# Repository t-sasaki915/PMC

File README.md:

# PrimitiveMemoryComputer
An AVR-based 8-bit single-board computer for direct memory programming.

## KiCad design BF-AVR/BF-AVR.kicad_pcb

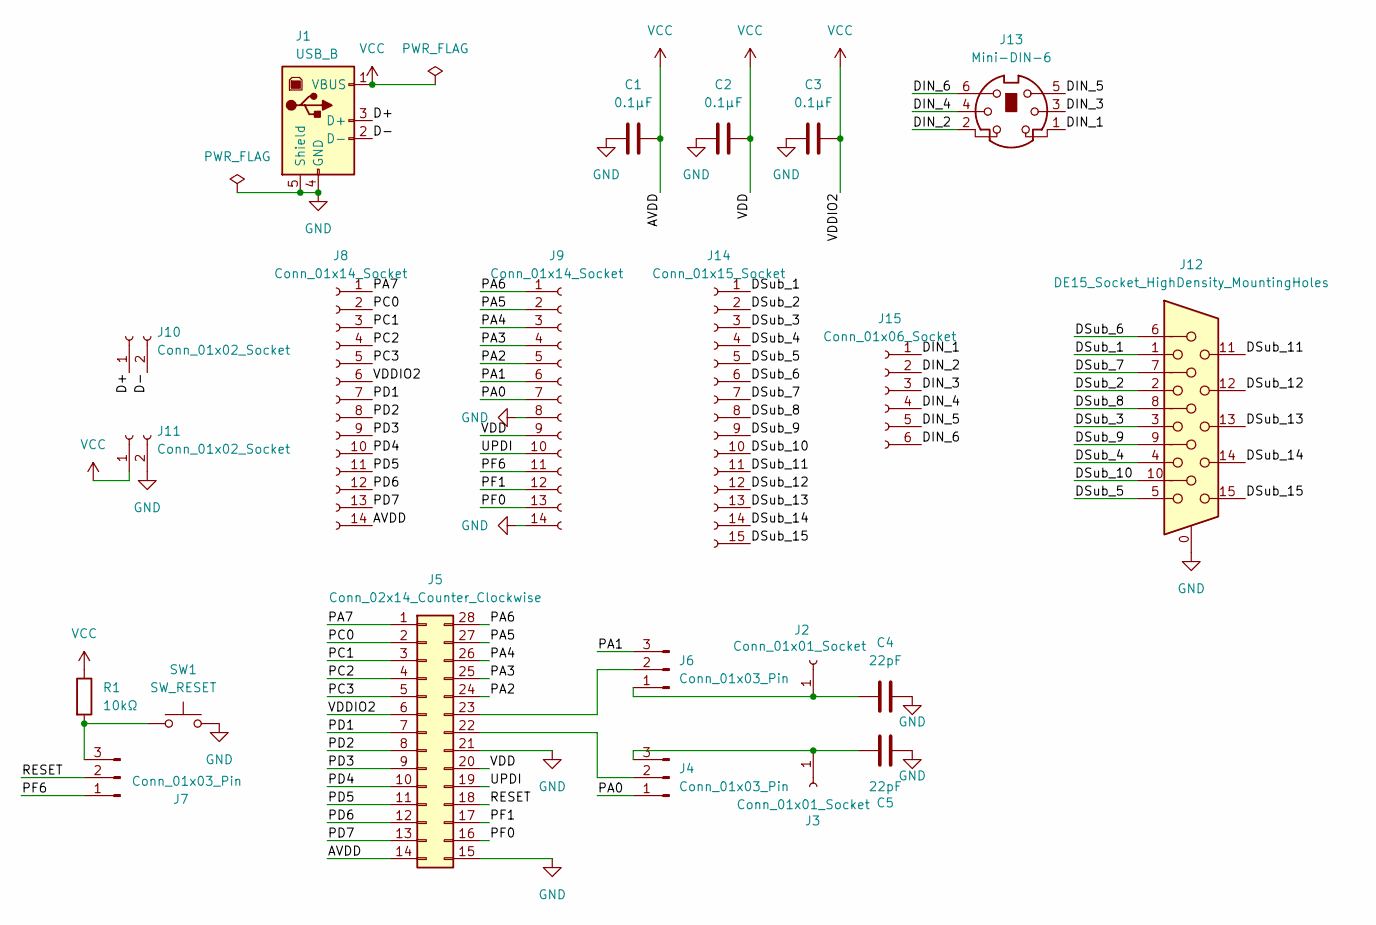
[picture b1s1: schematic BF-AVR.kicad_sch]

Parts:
C1, C2, C3: 0.1μF; C_Disc_D3.0mm_W2.0mm_P2.50mm
C4, C5: 22pF; C_Disc_D3.0mm_W2.0mm_P2.50mm
J1: USB_B; USB_B_Lumberg_2411_02_Horizontal
J2, J3: Conn_01x01_Socket; PinSocket_1x01_P2.54mm_Vertical
J4, J6, J7: Conn_01x03_Pin; PinHeader_1x03_P2.54mm_Vertical
J5: Conn_02x14_Counter_Clockwise; DIP-28_W7.62mm
J8, J9: Conn_01x14_Socket; PinSocket_1x14_P2.54mm_Vertical
J10, J11: Conn_01x02_Socket; PinSocket_1x02_P2.54mm_Vertical
J12: DE15_Socket_HighDensity_MountingHoles; DSUB-15-HD_Socket_Horizontal_P2.29x2.54mm_EdgePinOffset8.35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
J13: Mini-DIN-6; Connector_Mini-DIN_Female_6Pin_2rows
J14: Conn_01x15_Socket; PinSocket_1x15_P2.54mm_Vertical
J15: Conn_01x06_Socket; PinSocket_1x06_P2.54mm_Vertical
R1: 10kΩ; R_Axial_DIN0207_L6.3mm_D2.5mm_P7.62mm_Horizontal
SW1: SW_RESET; SW_PUSH_6mm_H4.3mm

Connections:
/D+: J1.3 (D+), J10.1
/D-: J1.2 (D-), J10.2
/DIN_1: J13.1, J15.1
/DIN_2: J13.2, J15.2
/DIN_3: J13.3, J15.3
/DIN_4: J13.4, J15.4
/DIN_5: J13.5, J15.5
/DIN_6: J13.6, J15.6
/DSub_1: J12.1, J14.1
/DSub_2: J12.2, J14.2
/DSub_3: J12.3, J14.3
/DSub_4: J12.4, J14.4
/DSub_5: J12.5, J14.5
/DSub_6: J12.6, J14.6
/DSub_7: J12.7, J14.7
/DSub_8: J12.8, J14.8
/DSub_9: J12.9, J14.9
/DSub_10: J12.10, J14.10
/DSub_11: J12.11, J14.11
/DSub_12: J12.12, J14.12
/DSub_13: J12.13, J14.13
/DSub_14: J12.14, J14.14
/DSub_15: J12.15, J14.15
/PA0: J4.1, J9.7
/PA1: J6.3, J9.6
/PA2: J5.24, J9.5
/PA3: J5.25, J9.4
/PA4: J5.26, J9.3
/PA5: J5.27, J9.2
/PA6: J5.28, J9.1
/PA7: J5.1, J8.1
/PC0: J5.2, J8.2
/PC1: J5.3, J8.3
/PC2: J5.4, J8.4
/PC3: J5.5, J8.5
/PD1: J5.7, J8.7
/PD2: J5.8, J8.8
/PD3: J5.9, J8.9
/PD4: J5.10, J8.10
/PD5: J5.11, J8.11
/PD6: J5.12, J8.12
/PD7: J5.13, J8.13
/PF0: J5.16, J9.13
/PF1: J5.17, J9.12
/PF6: J7.1, J9.11
/RESET: J5.18, J7.2
/UPDI: J5.19, J9.10
GND: C1.1, C2.1, C3.1, C4.2, C5.2, J1.4 (GND), J1.5 (Shield), J5.15, J5.21, J9.8, J9.14, J11.2, J12.0, SW1.2
unnamed: C4.1, J2.1, J6.1
unnamed: C5.1, J3.1, J4.3
unnamed: J4.2, J5.22
unnamed: J5.23, J6.2
unnamed: J7.3, R1.2, SW1.1
VCC: C1.2, C2.2, C3.2, J1.1 (VBUS), J5.6, J5.14, J5.20, J8.6, J8.14, J9.9, J11.1, R1.1

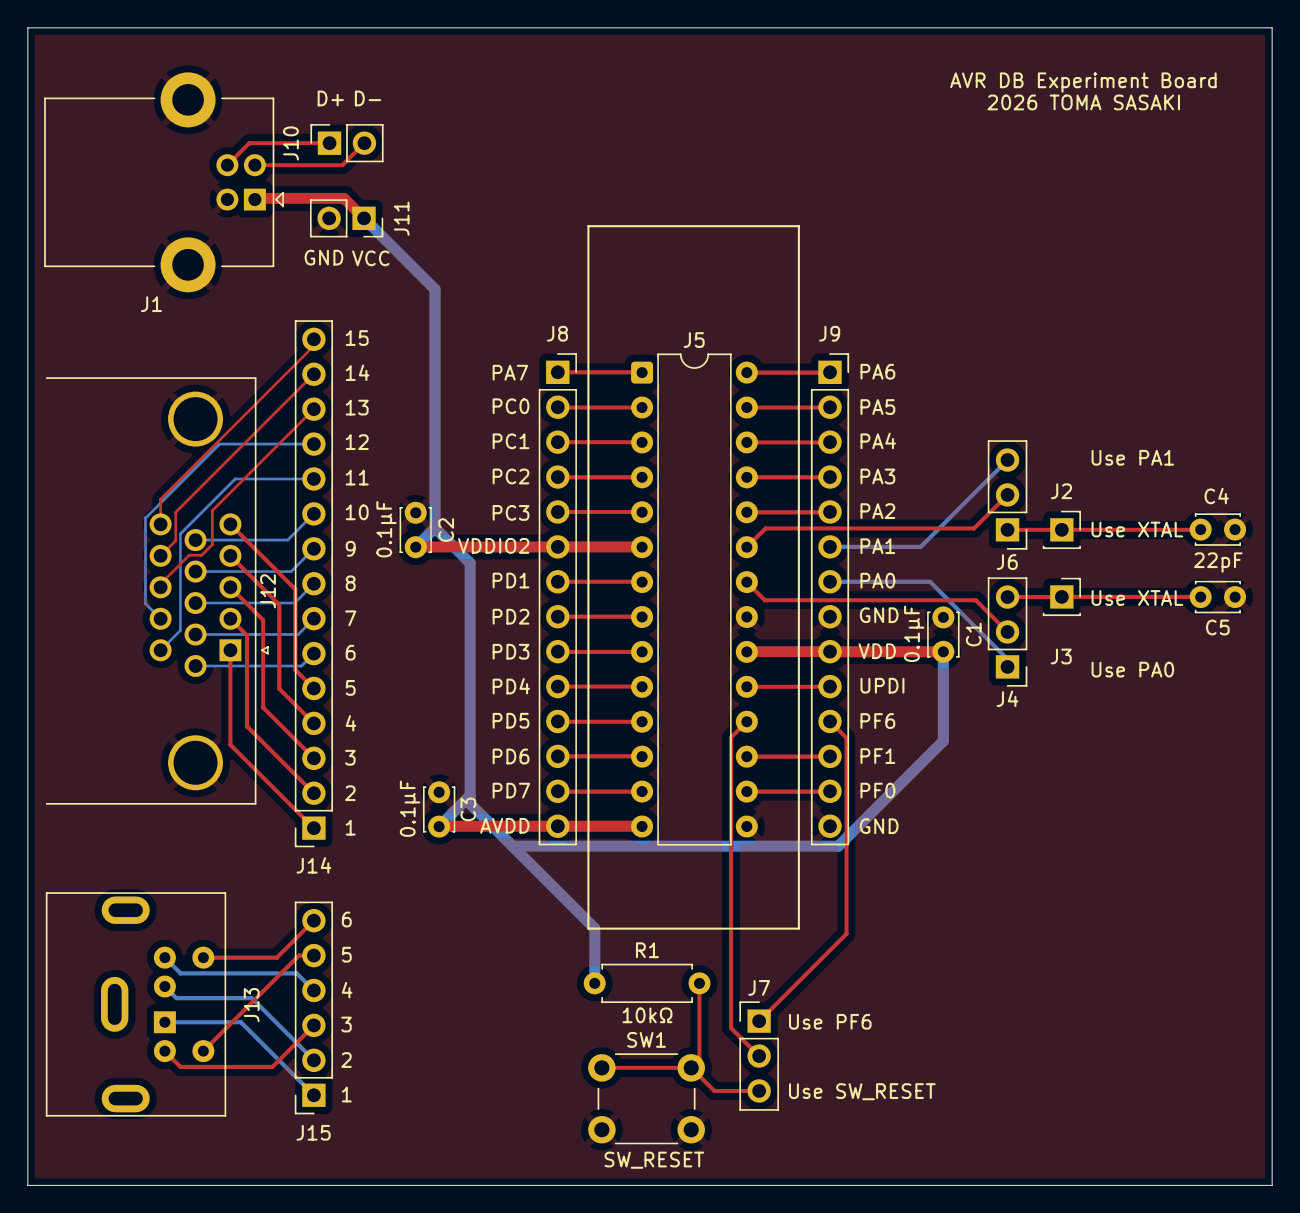
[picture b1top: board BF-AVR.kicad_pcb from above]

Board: 2 copper layers, 90.5 x 84.2 mm, 22 parts (0 on the bottom side), 54 nets.

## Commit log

2026-04-10 Rename project to PrimitiveMemoryComputer
    Updated project name and description in README.
